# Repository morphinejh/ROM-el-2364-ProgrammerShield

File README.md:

# Arduino Shield Programmer for ROM-el 2364
## Updates / Changes September 2023
* Added schematic for Arduino Shield
    * Test on: Duemilanove, Uno R3, and Mega R3
* Updated Arduino code and Python script data types to extend them to 32-bits for AT49F001 which has 17-bit addressing for the full range.
    * Added basic time duration to displayed output
    * Pin header to attach address
* Tested on Windows and Linux with Python 3
    * Comm port address is now a variable
* [Shared on OSH park](https://oshpark.com/shared_projects/amO60ueQ)

# ROM-el 2364 Programmer

This is an Arduino sketch and companion Python application to read from and write to ROM-el 2364 devices that (as of June 2018) ship with the AT49F512 EEPROM chip. It should, however ,also work with the AT49F001 EEPROM that was originally shipped on the ROM-el 2364.

The Python script was written and tested on a Linux system, and may need some tweaks to run in Windows environments, such as changing the serial port in the init_arduino() routine from /dev/ttyACM0 to, i.e. COM1.

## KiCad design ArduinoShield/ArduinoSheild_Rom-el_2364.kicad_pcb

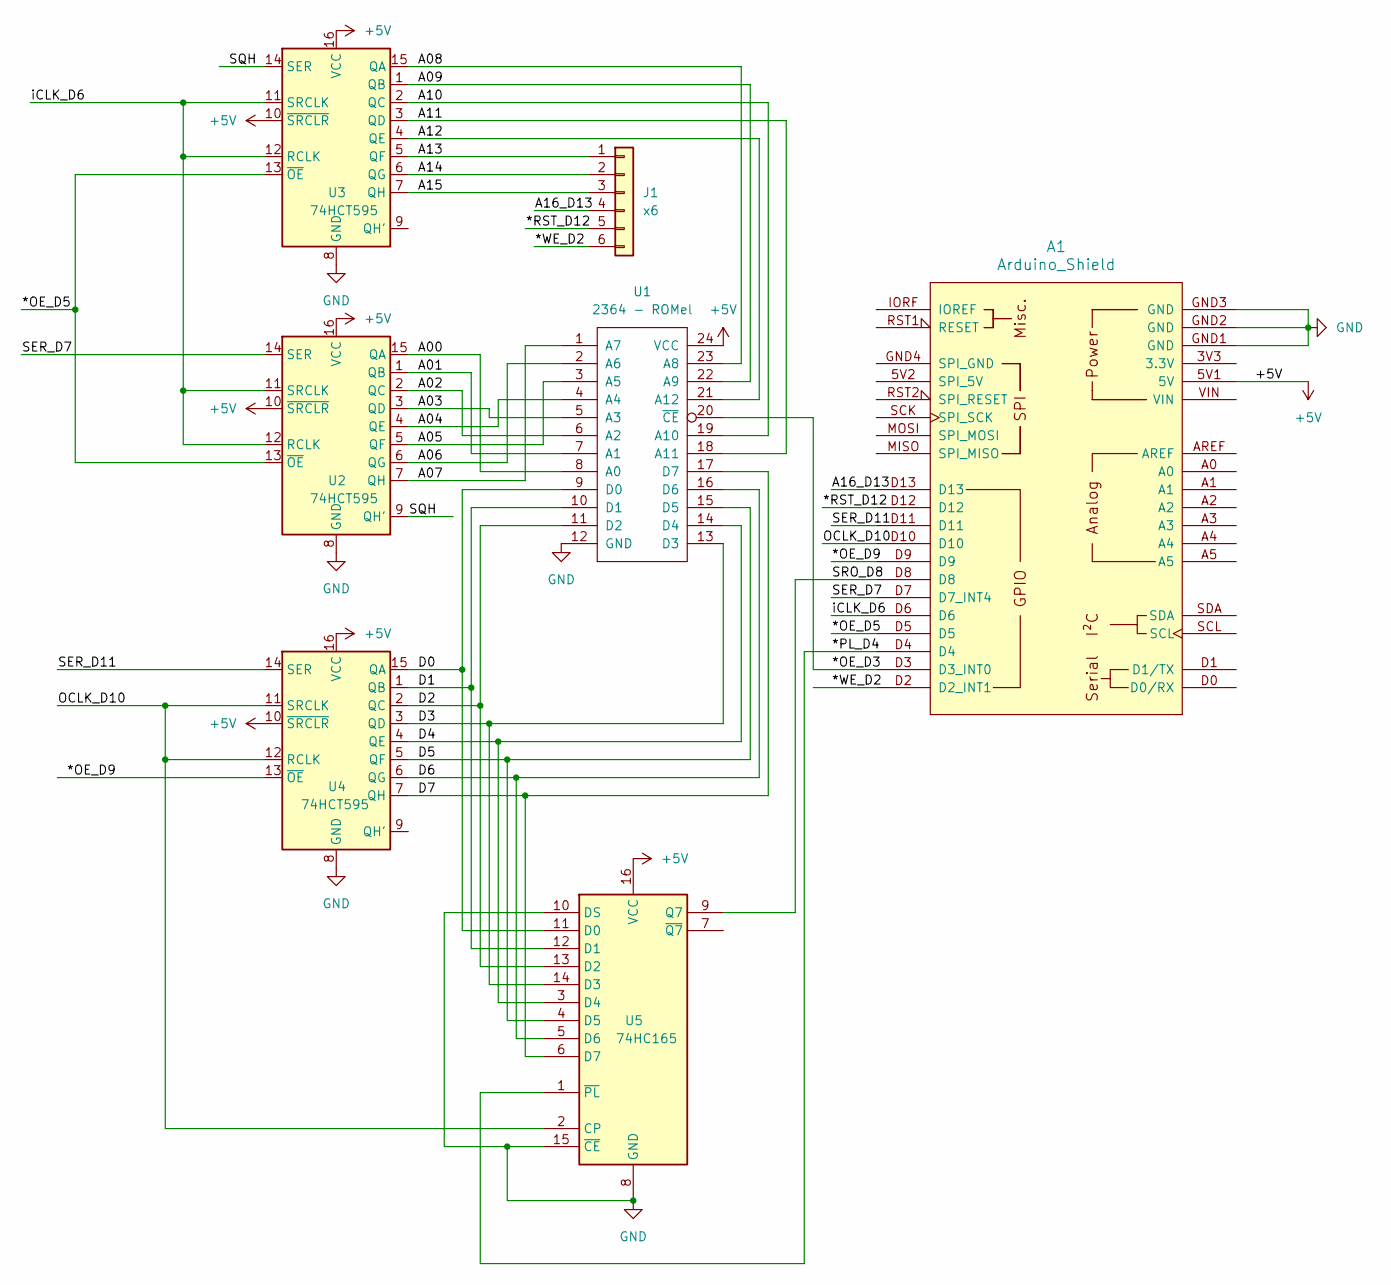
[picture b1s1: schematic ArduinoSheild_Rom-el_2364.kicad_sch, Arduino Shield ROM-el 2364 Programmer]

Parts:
A1: Arduino_Shield; Arduino_Leonardo_Shield
J1: x6; PinHeader_1x06_P2.54mm_Vertical
U1: 2364 - ROMel; DIP-24_W15.24mm-Notch
U2, U3, U4: 74HCT595; DIP-16_W7.62mm
U5: 74HC165; DIP-16_W7.62mm

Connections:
+5V: A1.5V1 (5V), U1.24 (VCC), U2.10 (~SRCLR), U2.16 (VCC), U3.10 (~SRCLR), U3.16 (VCC), U4.10 (~SRCLR), U4.16 (VCC), U5.16 (VCC)
/*CE_D3: A1.D3 (D3_INT0), U1.20 (~CE)
/*OE_D5: A1.D5, U2.13 (~OE), U3.13 (~OE)
/*OE_D9: A1.D9, U4.13 (~OE)
/*PL_D4: A1.D4, U5.1 (~PL)
/*RST_D12: A1.D12, J1.5
/*WE_D2: A1.D2 (D2_INT1), J1.6
/A00: U1.8 (A0), U2.15 (QA)
/A01: U1.7 (A1), U2.1 (QB)
/A02: U1.6 (A2), U2.2 (QC)
/A03: U1.5 (A3), U2.3 (QD)
/A04: U1.4 (A4), U2.4 (QE)
/A05: U1.3 (A5), U2.5 (QF)
/A06: U1.2 (A6), U2.6 (QG)
/A07: U1.1 (A7), U2.7 (QH)
/A08: U1.23 (A8), U3.15 (QA)
/A09: U1.22 (A9), U3.1 (QB)
/A10: U1.19 (A10), U3.2 (QC)
/A11: U1.18 (A11), U3.3 (QD)
/A12: U1.21 (A12), U3.4 (QE)
/A13: J1.1, U3.5 (QF)
/A14: J1.2, U3.6 (QG)
/A15: J1.3, U3.7 (QH)
/A16_D13: A1.D13, J1.4
/D0: U1.9 (D0), U4.15 (QA), U5.11 (D0)
/D1: U1.10 (D1), U4.1 (QB), U5.12 (D1)
/D2: U1.11 (D2), U4.2 (QC), U5.13 (D2)
/D3: U1.13 (D3), U4.3 (QD), U5.14 (D3)
/D4: U1.14 (D4), U4.4 (QE), U5.3 (D4)
/D5: U1.15 (D5), U4.5 (QF), U5.4 (D5)
/D6: U1.16 (D6), U4.6 (QG), U5.5 (D6)
/D7: U1.17 (D7), U4.7 (QH), U5.6 (D7)
/OCLK_D10: A1.D10, U4.11 (SRCLK), U4.12 (RCLK), U5.2 (CP)
/SER_D7: A1.D7 (D7_INT4), U2.14 (SER)
/SER_D11: A1.D11, U4.14 (SER)
/SQH: U2.9 (QH'), U3.14 (SER)
/SRO_D8: A1.D8, U5.9 (Q7)
/iCLK_D6: A1.D6, U2.11 (SRCLK), U2.12 (RCLK), U3.11 (SRCLK), U3.12 (RCLK)
GND: A1.GND1 (GND), A1.GND2 (GND), A1.GND3 (GND), U1.12 (GND), U2.8 (GND), U3.8 (GND), U4.8 (GND), U5.8 (GND), U5.10 (DS), U5.15 (~CE)

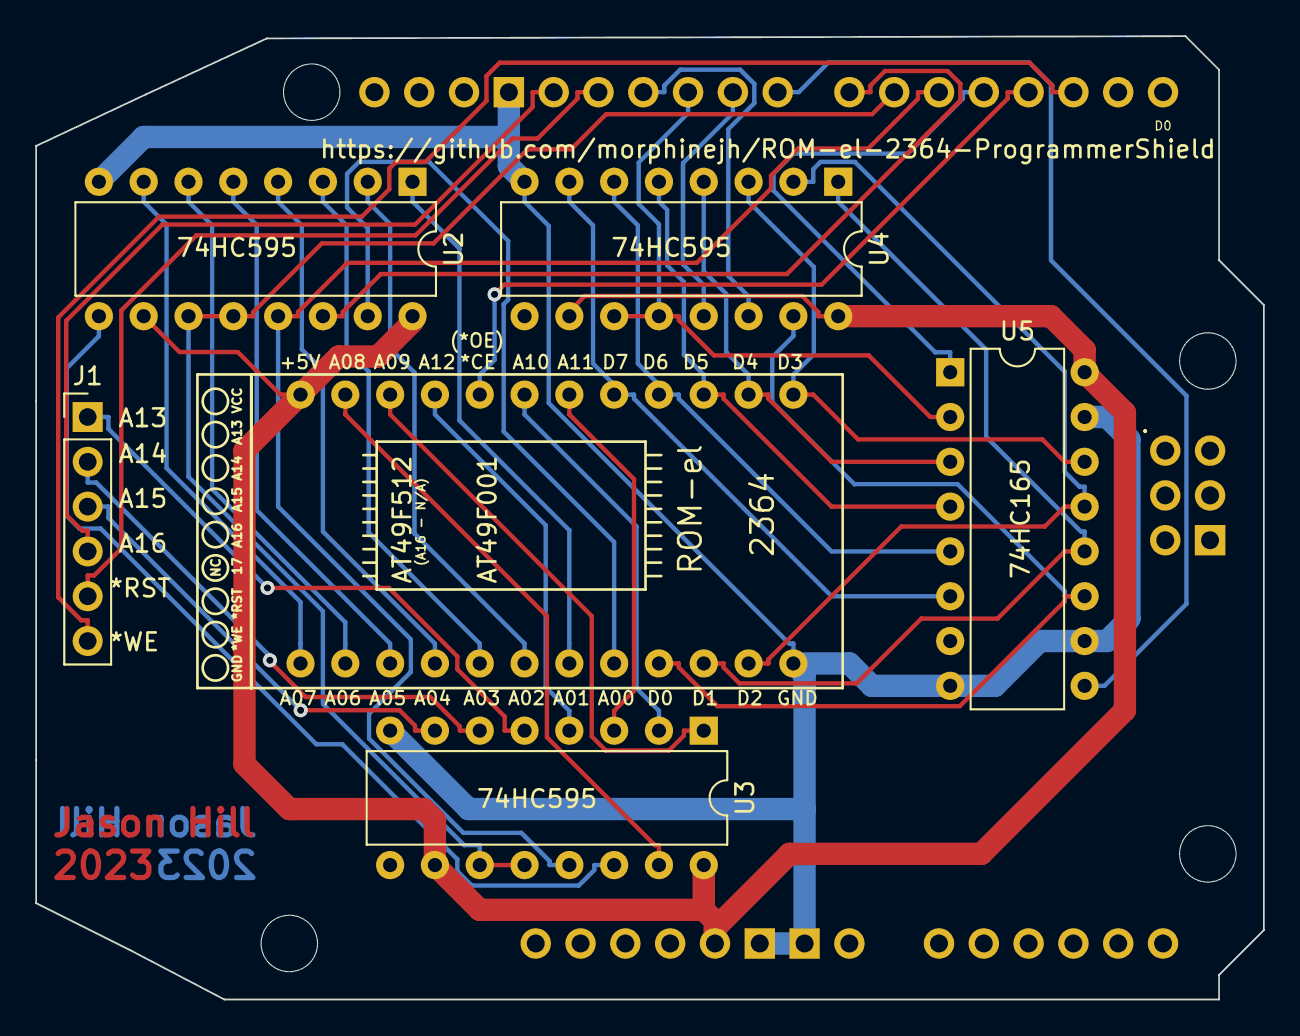
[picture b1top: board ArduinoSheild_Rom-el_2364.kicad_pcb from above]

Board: 2 copper layers, 69.6 x 54.6 mm, 7 parts (0 on the bottom side), 39 nets.

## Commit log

2023-09-13 Initial Revision of Arduino Shield Programmer
    Created a schematic for Arduino shield, extended address data type to 32-bits, and updated Arduino Code and Python script to use it.
2023-09-13 Create LICENSE
2023-10-15 Clean-up and corrections
